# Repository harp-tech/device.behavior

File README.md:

## Harp Behavior
This is a multi-purpose device tailored to behavioral experiments. It allows control of pokes, RGB LEDs, LEDs, cameras, servo motors and a quadrature counter.

### Key Features ###

* Enable pulse and configure duration for each output
* Support for PWM configuration (frequency up to 10KHz and duty cycle)
* LED current (up to 100mA) and maximum nominal current configuration
* Up to 2 cameras controlling (DO0 and DO1)
* Up to 2 servo motors (DO2 and DO3)
* Up to 1 quadrature counter (Port2) (Note: Port0 and Port1 can also act as quadrature counters but this is a request feature)

### Connectivity ###

* 1x clock sync input (CLKIN) [stereo jack]
* 1x USB (for computer) [USB type B]
* 1x 12V supply [barrel connector jack]
* 3x poke connectors (LED+12V valve) (Poke0, Poke1, Poke2) [RJ45]
* 2x LEDs outputs (5V) (LED0, LED1) [screw terminal]
* 2x RGB LEDs outputs (5V) (RGB0, RGB1) [flick lock 3x male pins]
* 4x general purpose digital outputs with PWM (5V) (DO0-DO3) [screw terminal]
* 1x ADC (5V) [screw terminal]

## Interface ##

The interface with the Harp Behavior can be done through [Bonsai](https://bonsai-rx.org/) or a dedicated GUI (Graphical User Interface).

## Licensing ##

Each subdirectory will contain a license or, possibly, a set of licenses if it involves both hardware and software.

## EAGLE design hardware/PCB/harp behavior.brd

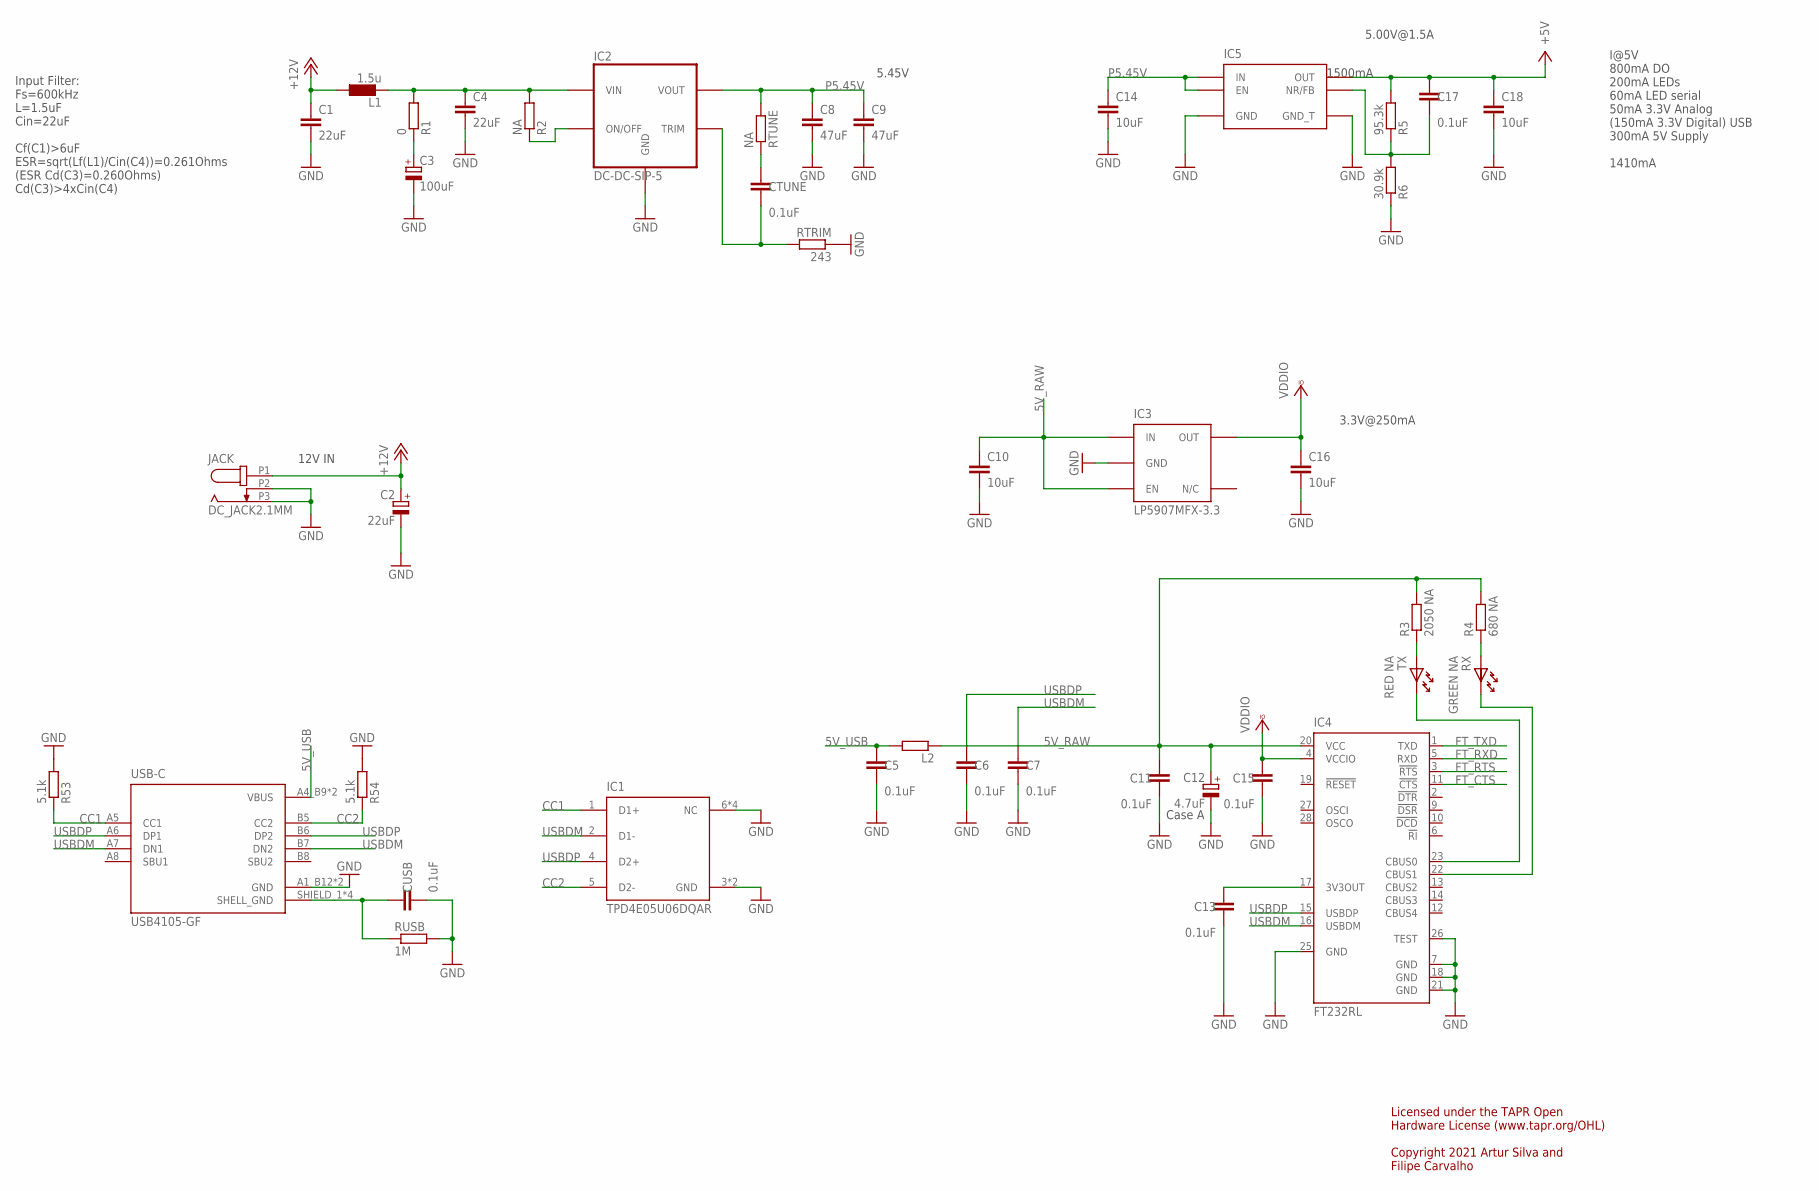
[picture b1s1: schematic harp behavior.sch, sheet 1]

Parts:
C1, C4: 22uF; C1210
C2: 22uF; CAP_100UF_HAND
C3: 100uF; PANASONIC_E
C5, C6, C7, C11, C13, C15, C17: 0.1uF; 0402-TIGHT
C8, C9: 47uF; C1210
C10, C14, C16, C18: 10uF; C0603
C12: 4.7uF; A/3216-18W
CTUNE: 0.1uF; 0402-TIGHT
CUSB: 0.1uF; 0402-TIGHT
IC1: TPD4E05U06DQAR; USON10
IC2: DC-DC-SIP-5; SIP-5
IC3: LP5907MFX-3.3; TSOT23-5
IC4: FT232RL; SSOP28
IC5: TPS78601SON; SON-8
JACK: DC_JACK2.1MM; DC_POWER_INPUT_2.1MM
L1: 1.5u; IND_LPS4012_V2
L2: ???; R0805
R1: 0; R0402
R2: NA; R0402
R3: 2050 NA; R0402
R4: 680 NA; R0402
R5: 95.3k; R0402
R6: 30.9k; R0402
R53, R54: 5.1k; R0402
RTRIM: 243; R0402
RTUNE: NA; R0402
RUSB: 1M; R0402
RX: GREEN NA; LED_HAND
TX: RED NA; LED_HAND
USB-C: USB4105-GF; USB4105-GF-A

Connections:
5V_RAW: C10.1, C11.1, C12.+, IC3.1 (IN), IC3.3 (EN), IC4.20 (VCC), L2.1, R3.2, R4.2
5V_USB: C5.1, L2.2, USB-C.A4_B9 (VBUS), USB-C.B4_A9 (VBUS)
+5V: C17.1, C18.1, IC5.P3 (OUT), IC5.P4 (OUT), R5.2; also elsewhere on the board
+12V: C1.1, C2.+, JACK.P1 (1), L1.1; also elsewhere on the board
CC1: IC1.1 (D1+), R53.1, USB-C.A5 (CC1)
CC2: IC1.5 (D2-), R54.1, USB-C.B5 (CC2)
DCIN: C4.1, IC2.P2 (VIN), L1.2, R1.2, R2.2
FT_CTS: IC4.11 (!CTS); also elsewhere on the board
FT_RTS: IC4.3 (!RTS); also elsewhere on the board
FT_RXD: IC4.5 (RXD); also elsewhere on the board
FT_TXD: IC4.1 (TXD); also elsewhere on the board
GND: C1.2, C2.-, C3.-, C4.2, C5.2, C6.2, C7.2, C8.2, C9.2, C10.2, C11.2, C12.-, C13.2, C14.2, C15.2, C16.2, C18.2, CUSB.2, IC1.3 (GND), IC1.6 (NC), IC1.7 (NC), IC1.8 (GND), IC1.9 (NC), IC1.10 (NC), IC2.P3 (GND), IC3.2 (GND), IC4.7 (GND), IC4.18 (GND), IC4.21 (GND), IC4.25 (GND), IC4.26 (TEST), IC5.P6 (GND), IC5.P9 (GND_T), JACK.P2 (2), JACK.P3 (3), R6.1, R53.2, R54.2, RTRIM.1, RUSB.2, USB-C.A1_B12 (GND), USB-C.B1_A12 (GND); also elsewhere on the board
unnamed: CTUNE.2, IC2.P5 (TRIM), RTRIM.2
unnamed: CTUNE.1, RTUNE.1
unnamed: IC2.P1 (ON/OFF), R2.1
unnamed: C17.2, IC5.P5 (NR/FB), R5.1, R6.2
unnamed: C3.+, R1.1
unnamed: CUSB.1, RUSB.1, USB-C.SHIELD_1 (SHELL_GND), USB-C.SHIELD_2 (SHELL_GND), USB-C.SHIELD_3 (SHELL_GND), USB-C.SHIELD_4 (SHELL_GND)
unnamed: C13.1, IC4.17 (3V3OUT)
unnamed: R4.1, RX.A
unnamed: IC4.23 (CBUS0), TX.K
unnamed: IC4.22 (CBUS1), RX.K
unnamed: R3.1, TX.A
P5.45V: C8.1, C9.1, C14.1, IC2.P4 (VOUT), IC5.P1 (IN), IC5.P2 (IN), IC5.P8 (EN), RTUNE.2
USBDM: C7.1, IC1.2 (D1-), IC4.16 (USBDM), USB-C.A7 (DN1), USB-C.B7 (DN2)
USBDP: C6.1, IC1.4 (D2+), IC4.15 (USBDP), USB-C.A6 (DP1), USB-C.B6 (DP2)
VCCIO: C15.1, C16.1, IC3.5 (OUT), IC4.4 (VCCIO); also elsewhere on the board

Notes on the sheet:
Case A
3.3V@250mA
Licensed under the TAPR Open Hardware License (www.tapr.org/OHL) Copyright 2021 Artur Silva and Filipe Carvalho
12V IN
I@5V 800mA DO 200mA LEDs 60mA LED serial 50mA 3.3V Analog (150mA 3.3V Digital) USB 300mA 5V Supply 1410mA
5.45V
1500mA
5.00V@1.5A
Input Filter: Fs=600kHz L=1.5uF Cin=22uF Cf(C1)>6uF ESR=sqrt(Lf(L1)/Cin(C4))=0.261Ohms (ESR Cd(C3)=0.260Ohms) Cd(C3)>4xCin(C4)

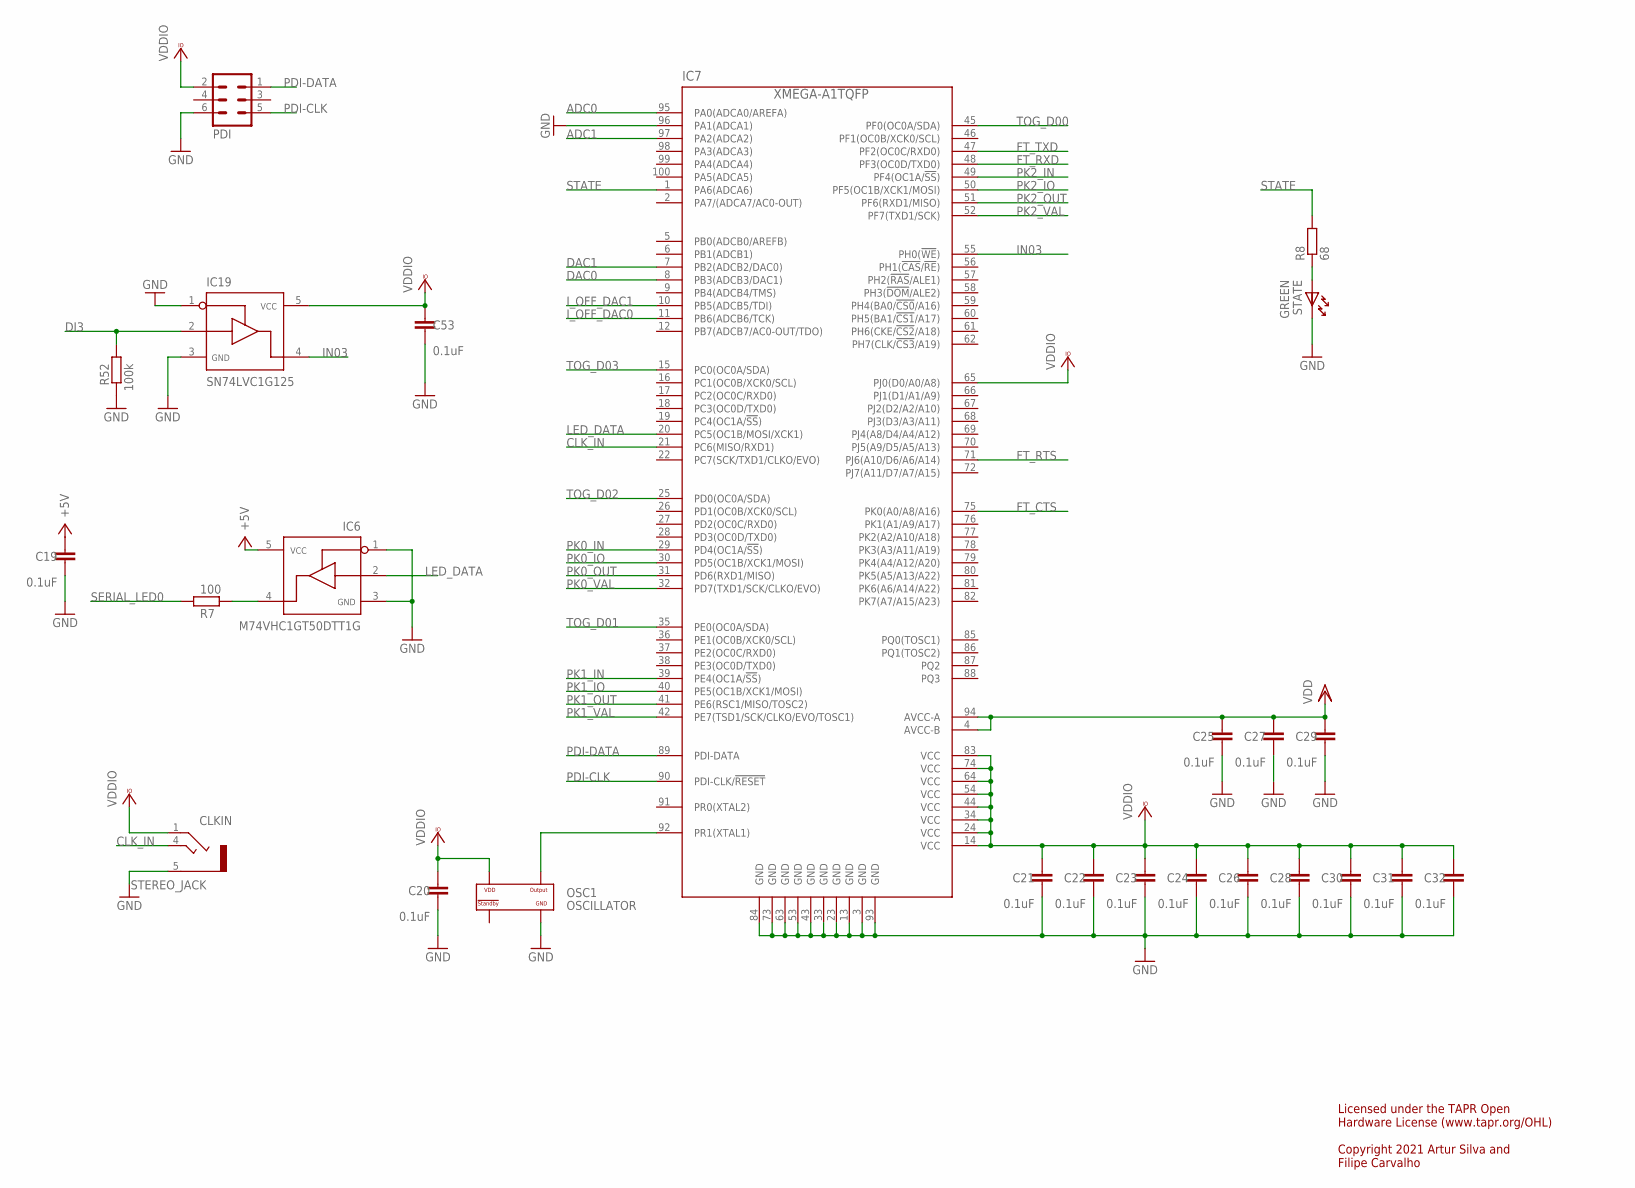
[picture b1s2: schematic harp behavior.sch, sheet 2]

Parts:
C19, C20, C21, C22, C23, C24, C25, C26, C27, C28, C29, C30, C31, C32, C53: 0.1uF; 0402-TIGHT
CLKIN: STEREO_JACK; 35RASMT2BHNTRX
IC6: M74VHC1GT50DTT1G; SOT23-5
IC7: XMEGA-A1TQFP; TQFP100
IC19: SN74LVC1G125; SOT23-5
OSC1: OSCILLATOR; OSCILLATOR_3.2X2.5
PDI: MA03-2
R7: 100; R0402
R8: 68; R0402
R52: 100k; R0402
STATE: GREEN; LED_HAND

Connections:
+5V: C19.1, IC6.5; also elsewhere on the board
ADC0: IC7.95 (PA0(ADCA0/AREFA)); also elsewhere on the board
ADC1: IC7.97 (PA2(ADCA2)); also elsewhere on the board
CLK_IN: CLKIN.4, IC7.21 (PC6(MISO/RXD1))
DAC0: IC7.8 (PB3(ADCB3/DAC1)); also elsewhere on the board
DAC1: IC7.7 (PB2(ADCB2/DAC0)); also elsewhere on the board
DI3: IC19.2, R52.1; also elsewhere on the board
FT_CTS: IC7.75 (PK0(A0/A8/A16)); also elsewhere on the board
FT_RTS: IC7.71 (PJ6(A10/D6/A6/A14)); also elsewhere on the board
FT_RXD: IC7.48 (PF3(OC0D/TXD0)); also elsewhere on the board
FT_TXD: IC7.47 (PF2(OC0C/RXD0)); also elsewhere on the board
GND: C19.2, C20.2, C21.2, C22.2, C23.2, C24.2, C25.2, C26.2, C27.2, C28.2, C29.2, C30.2, C31.2, C32.2, C53.2, CLKIN.5, IC6.1, IC6.3, IC7.3 (GND), IC7.13 (GND), IC7.23 (GND), IC7.33 (GND), IC7.43 (GND), IC7.53 (GND), IC7.63 (GND), IC7.73 (GND), IC7.84 (GND), IC7.93 (GND), IC7.96 (PA1(ADCA1)), IC19.1, IC19.3, OSC1.P$2 (GND), PDI.6, R52.2, STATE.K; also elsewhere on the board
IN03: IC7.55 (PH0(!WE!)), IC19.4
I_OFF_DAC0: IC7.11 (PB6(ADCB6/TCK)); also elsewhere on the board
I_OFF_DAC1: IC7.10 (PB5(ADCB5/TDI)); also elsewhere on the board
LED_DATA: IC6.2, IC7.20 (PC5(OC1B/MOSI/XCK1))
unnamed: IC6.4, R7.2
unnamed: R8.1, STATE.A
OSC1: IC7.92 (PR1(XTAL1)), OSC1.P$3 (OUTPUT)
PDI-CLK: IC7.90 (PDI-CLK/!RESET), PDI.5
PDI-DATA: IC7.89 (PDI-DATA), PDI.1
PK0_IN: IC7.29 (PD4(OC1A/!SS!)); also elsewhere on the board
PK0_IO: IC7.30 (PD5(OC1B/XCK1/MOSI)); also elsewhere on the board
PK0_OUT: IC7.31 (PD6(RXD1/MISO)); also elsewhere on the board
PK0_VAL: IC7.32 (PD7(TXD1/SCK/CLKO/EVO)); also elsewhere on the board
PK1_IN: IC7.39 (PE4(OC1A/!SS!)); also elsewhere on the board
PK1_IO: IC7.40 (PE5(OC1B/XCK1/MOSI)); also elsewhere on the board
PK1_OUT: IC7.41 (PE6(RSC1/MISO/TOSC2)); also elsewhere on the board
PK1_VAL: IC7.42 (PE7(TSD1/SCK/CLKO/EVO/TOSC1)); also elsewhere on the board
PK2_IN: IC7.49 (PF4(OC1A/!SS!)); also elsewhere on the board
PK2_IO: IC7.50 (PF5(OC1B/XCK1/MOSI)); also elsewhere on the board
PK2_OUT: IC7.51 (PF6(RXD1/MISO)); also elsewhere on the board
PK2_VAL: IC7.52 (PF7(TXD1/SCK)); also elsewhere on the board
SERIAL_LED0: R7.1; also elsewhere on the board
STATE: IC7.1 (PA6(ADCA6)), R8.2
TOG_D00: IC7.45 (PF0(OC0A/SDA)); also elsewhere on the board
TOG_D01: IC7.35 (PE0(OC0A/SDA)); also elsewhere on the board
TOG_D02: IC7.25 (PD0(OC0A/SDA)); also elsewhere on the board
TOG_D03: IC7.15 (PC0(OC0A/SDA)); also elsewhere on the board
VCCIO: C20.1, C21.1, C22.1, C23.1, C24.1, C26.1, C28.1, C30.1, C31.1, C32.1, C53.1, CLKIN.1, IC7.14 (VCC), IC7.24 (VCC), IC7.34 (VCC), IC7.44 (VCC), IC7.54 (VCC), IC7.64 (VCC), IC7.65 (PJ0(D0/A0/A8)), IC7.74 (VCC), IC7.83 (VCC), IC19.5, OSC1.P$4 (VDD), PDI.2; also elsewhere on the board
VDD: C25.1, C27.1, C29.1, IC7.4 (AVCC-B), IC7.94 (AVCC-A); also elsewhere on the board

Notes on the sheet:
Licensed under the TAPR Open Hardware License (www.tapr.org/OHL) Copyright 2021 Artur Silva and Filipe Carvalho

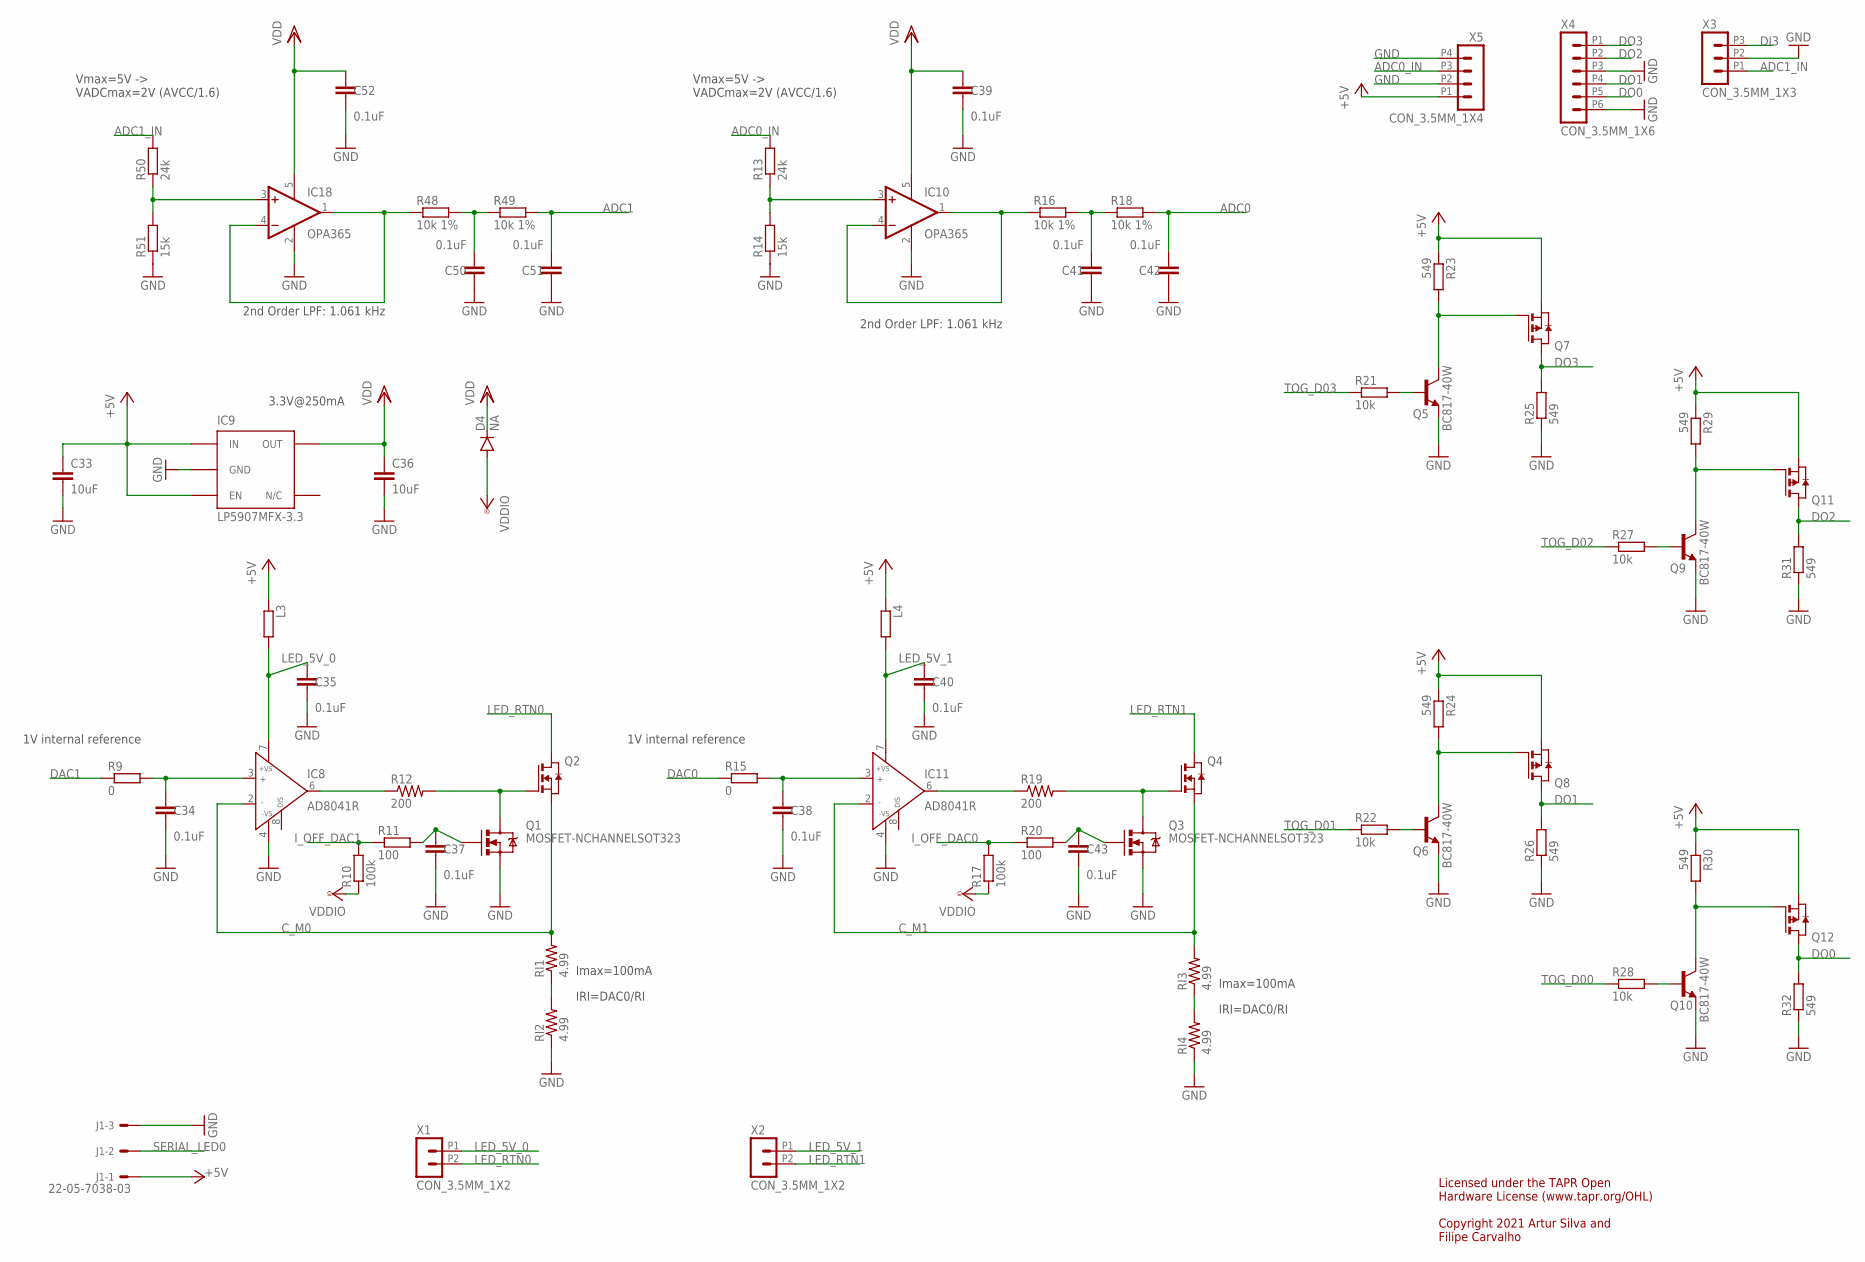
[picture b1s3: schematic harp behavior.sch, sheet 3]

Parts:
C33, C36: 10uF; C0603
C34, C35, C37, C38, C39, C40, C41, C42, C43, C50, C51, C52: 0.1uF; 0402-TIGHT
D4: NA; SOD-323-DIODE
IC8, IC11: AD8041R; SO8
IC9: LP5907MFX-3.3; TSOT23-5
IC10, IC18: OPA365; SOT23-5
J1: 22-05-7038-03; 7395-03
L3, L4: 600@100M; R0805
Q1, Q3: MOSFET-NCHANNELSOT323; SOT323
Q2, Q4: NMOSSOT223; SOT223
Q5, Q6, Q9, Q10: BC817-40W; SOT323-BEC
Q7, Q8, Q11, Q12: PMOSSOT223; SOT223
R9, R15: 0; R0402
R10, R17: 100k; R0402
R11, R20: 100; R0402
R12, R19: 200; R1210
R13, R50: 24k; R0402
R14, R51: 15k; R0402
R16, R18, R48, R49: 10k 1%; R0402
R21, R22, R27, R28: 10k; R0402
R23, R24, R25, R26, R29, R30, R31, R32: 549; R0805
RI1, RI2, RI3, RI4: 4.99; R2512
X1, X2: CON_3.5MM_1X2
X3: CON_3.5MM_1X3
X4: CON_3.5MM_1X6
X5: CON_3.5MM_1X4

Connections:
+5V: C33.1, IC9.1 (IN), IC9.3 (EN), J1.1, L3.1, L4.1, Q7.3 (S), Q8.3 (S), Q11.3 (S), Q12.3 (S), R23.1, R24.1, R29.1, R30.1, X5.P1 (1); also elsewhere on the board
ADC0: C42.2, R18.2; also elsewhere on the board
ADC0_IN: R13.2, X5.P3 (3)
ADC1: C51.2, R49.2; also elsewhere on the board
ADC1_IN: R50.2, X3.P1 (1)
CTRL_BL: IC11.6 (OUT), R19.1
CTRL_BL1: IC8.6 (OUT), R12.1
C_M0: IC8.2 (IN-), Q2.3 (S), RI1.2
C_M1: IC11.2 (IN-), Q4.3 (S), RI3.2
DAC0: R15.1; also elsewhere on the board
DAC1: R9.1; also elsewhere on the board
DI3: X3.P3 (3); also elsewhere on the board
DO0: Q12.2 (D), Q12.4 (D), R32.2, X4.P5 (5)
DO1: Q8.2 (D), Q8.4 (D), R26.2, X4.P4 (4)
DO2: Q11.2 (D), Q11.4 (D), R31.2, X4.P2 (2)
DO3: Q7.2 (D), Q7.4 (D), R25.2, X4.P1 (1)
GND: C33.2, C34.2, C35.2, C36.2, C37.2, C38.2, C39.2, C40.2, C41.1, C42.1, C43.2, C50.1, C51.1, C52.2, IC8.4 (-VS), IC9.2 (GND), IC10.2 (V-), IC11.4 (-VS), IC18.2 (V-), J1.3, Q1.2 (S), Q3.2 (S), Q5.E, Q6.E, Q9.E, Q10.E, R14.1, R25.1, R26.1, R31.1, R32.1, R51.1, RI2.1, RI4.1, X3.P2 (2), X4.P3 (3), X4.P6 (6), X5.P2 (2), X5.P4 (4); also elsewhere on the board
I_OFF_DAC0: R17.2, R20.1; also elsewhere on the board
I_OFF_DAC1: R10.2, R11.1; also elsewhere on the board
LED_5V_0: C35.1, IC8.7 (+VS), L3.2, X1.P1 (1)
LED_5V_1: C40.1, IC11.7 (+VS), L4.2, X2.P1 (1)
LED_RTN0: Q2.2 (D), Q2.4 (D), X1.P2 (2)
LED_RTN1: Q4.2 (D), Q4.4 (D), X2.P2 (2)
unnamed: Q3.3 (D), Q4.1 (G), R19.2
unnamed: Q6.C, Q8.1 (G), R24.2
unnamed: Q6.B, R22.2
unnamed: Q9.C, Q11.1 (G), R29.2
unnamed: Q9.B, R27.2
unnamed: Q10.C, Q12.1 (G), R30.2
unnamed: Q10.B, R28.2
unnamed: Q1.3 (D), Q2.1 (G), R12.2
unnamed: C34.1, IC8.3 (IN+), R9.2
unnamed: C50.2, R48.2, R49.1
unnamed: IC18.1 (OUT), IC18.4 (-IN), R48.1
unnamed: C38.1, IC11.3 (IN+), R15.2
unnamed: RI1.1, RI2.2
unnamed: Q5.C, Q7.1 (G), R23.2
unnamed: Q5.B, R21.2
unnamed: C37.1, Q1.1 (G), R11.2
unnamed: IC18.3 (+IN), R50.1, R51.2
unnamed: C43.1, Q3.1 (G), R20.2
unnamed: RI3.1, RI4.2
unnamed: C41.2, R16.2, R18.1
unnamed: IC10.1 (OUT), IC10.4 (-IN), R16.1
unnamed: IC10.3 (+IN), R13.1, R14.2
SERIAL_LED0: J1.2; also elsewhere on the board
TOG_D00: R28.1; also elsewhere on the board
TOG_D01: R22.1; also elsewhere on the board
TOG_D02: R27.1; also elsewhere on the board
TOG_D03: R21.1; also elsewhere on the board
VCCIO: D4.A, R10.1, R17.1; also elsewhere on the board
VDD: C36.1, C39.1, C52.1, D4.C, IC9.5 (OUT), IC10.5 (V+), IC18.5 (V+); also elsewhere on the board

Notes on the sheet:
IRI=DAC0/RI
2nd Order LPF: 1.061 kHz
Licensed under the TAPR Open Hardware License (www.tapr.org/OHL) Copyright 2021 Artur Silva and Filipe Carvalho
3.3V@250mA
Vmax=5V -> VADCmax=2V (AVCC/1.6)
Imax=100mA
1V internal reference

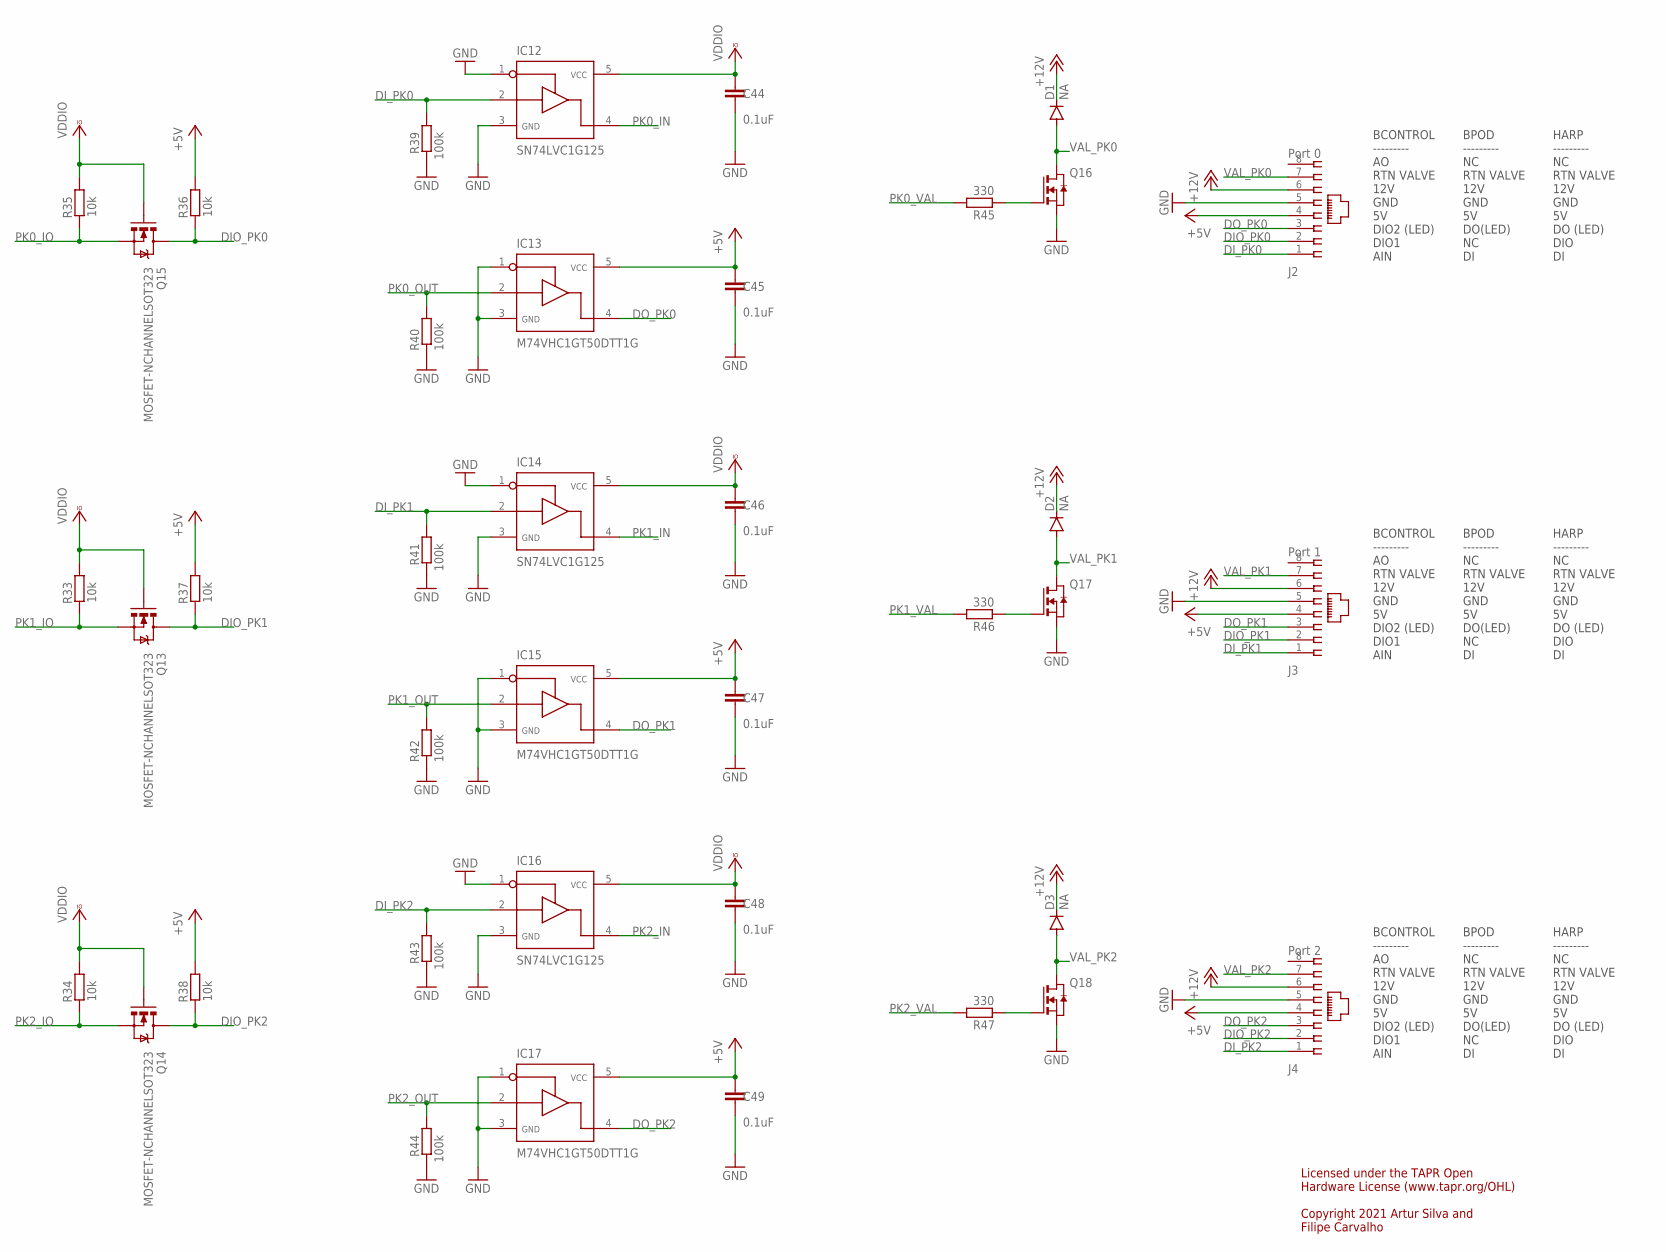
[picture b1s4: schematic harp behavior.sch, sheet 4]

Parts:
C44, C45, C46, C47, C48, C49: 0.1uF; 0402-TIGHT
D1, D2, D3: NA; SOD-323-DIODE
IC12, IC14, IC16: SN74LVC1G125; SOT23-5
IC13, IC15, IC17: M74VHC1GT50DTT1G; SOT23-5
J2: Port 0; 520426-4
J3: Port 1; 520426-4
J4: Port 2; 520426-4
Q13, Q14, Q15: MOSFET-NCHANNELSOT323; SOT323
Q16, Q17, Q18: NMOSSOT223; SOT223
R33, R34, R35, R36, R37, R38: 10k; R0402
R39, R40, R41, R42, R43, R44: 100k; R0402
R45, R46, R47: 330; R0402

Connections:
+5V: C45.1, C47.1, C49.1, IC13.5, IC15.5, IC17.5, J2.4, J3.4, J4.4, R36.1, R37.1, R38.1; also elsewhere on the board
+12V: D1.C, D2.C, D3.C, J2.6, J3.6, J4.6; also elsewhere on the board
DIO_PK0: J2.2, Q15.3 (D), R36.2
DIO_PK1: J3.2, Q13.3 (D), R37.2
DIO_PK2: J4.2, Q14.3 (D), R38.2
DI_PK0: IC12.2, J2.1, R39.1
DI_PK1: IC14.2, J3.1, R41.1
DI_PK2: IC16.2, J4.1, R43.1
DO_PK0: IC13.4, J2.3
DO_PK1: IC15.4, J3.3
DO_PK2: IC17.4, J4.3
GND: C44.2, C45.2, C46.2, C47.2, C48.2, C49.2, IC12.1, IC12.3, IC13.1, IC13.3, IC14.1, IC14.3, IC15.1, IC15.3, IC16.1, IC16.3, IC17.1, IC17.3, J2.5, J3.5, J4.5, Q16.3 (S), Q17.3 (S), Q18.3 (S), R39.2, R40.1, R41.2, R42.1, R43.2, R44.2; also elsewhere on the board
unnamed: Q16.1 (G), R45.2
unnamed: Q17.1 (G), R46.2
unnamed: Q18.1 (G), R47.2
PK0_IN: IC12.4; also elsewhere on the board
PK0_IO: Q15.2 (S), R35.2; also elsewhere on the board
PK0_OUT: IC13.2, R40.2; also elsewhere on the board
PK0_VAL: R45.1; also elsewhere on the board
PK1_IN: IC14.4; also elsewhere on the board
PK1_IO: Q13.2 (S), R33.2; also elsewhere on the board
PK1_OUT: IC15.2, R42.2; also elsewhere on the board
PK1_VAL: R46.1; also elsewhere on the board
PK2_IN: IC16.4; also elsewhere on the board
PK2_IO: Q14.2 (S), R34.2; also elsewhere on the board
PK2_OUT: IC17.2, R44.1; also elsewhere on the board
PK2_VAL: R47.1; also elsewhere on the board
VAL_PK0: D1.A, J2.7, Q16.2 (D), Q16.4 (D)
VAL_PK1: D2.A, J3.7, Q17.2 (D), Q17.4 (D)
VAL_PK2: D3.A, J4.7, Q18.2 (D), Q18.4 (D)
VCCIO: C44.1, C46.1, C48.1, IC12.5, IC14.5, IC16.5, Q13.1 (G), Q14.1 (G), Q15.1 (G), R33.1, R34.1, R35.1; also elsewhere on the board

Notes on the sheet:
BCONTROL --------- AO RTN VALVE 12V GND 5V DIO2 (LED) DIO1 AIN
BPOD --------- NC RTN VALVE 12V GND 5V DO(LED) NC DI
HARP --------- NC RTN VALVE 12V GND 5V DO (LED) DIO DI
Licensed under the TAPR Open Hardware License (www.tapr.org/OHL) Copyright 2021 Artur Silva and Filipe Carvalho

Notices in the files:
PCB modules/Light detector/light detector v2.3.sch:
Copyright 2018-2021 Artur Silva
Peripherals/Encoder/harp behavior encoder v1.2.brd:
Copyright 2021 Hardware Platform
Peripherals/Port Breakout/harp behavior poke port breakout v2.0.brd:
Copyright 2018-2022 Artur Silva and Filipe Carvalho
parts and their libraries:
SparkFun-Capacitors: Licensing: Creative Commons ShareAlike 4.0 International - https://creativecommons.org/licenses/by-sa/4.0
